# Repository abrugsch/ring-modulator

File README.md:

# ring-modulator
 ring modulator pedal created from https://www.instructables.com/Ring-Modulator-Pedal/

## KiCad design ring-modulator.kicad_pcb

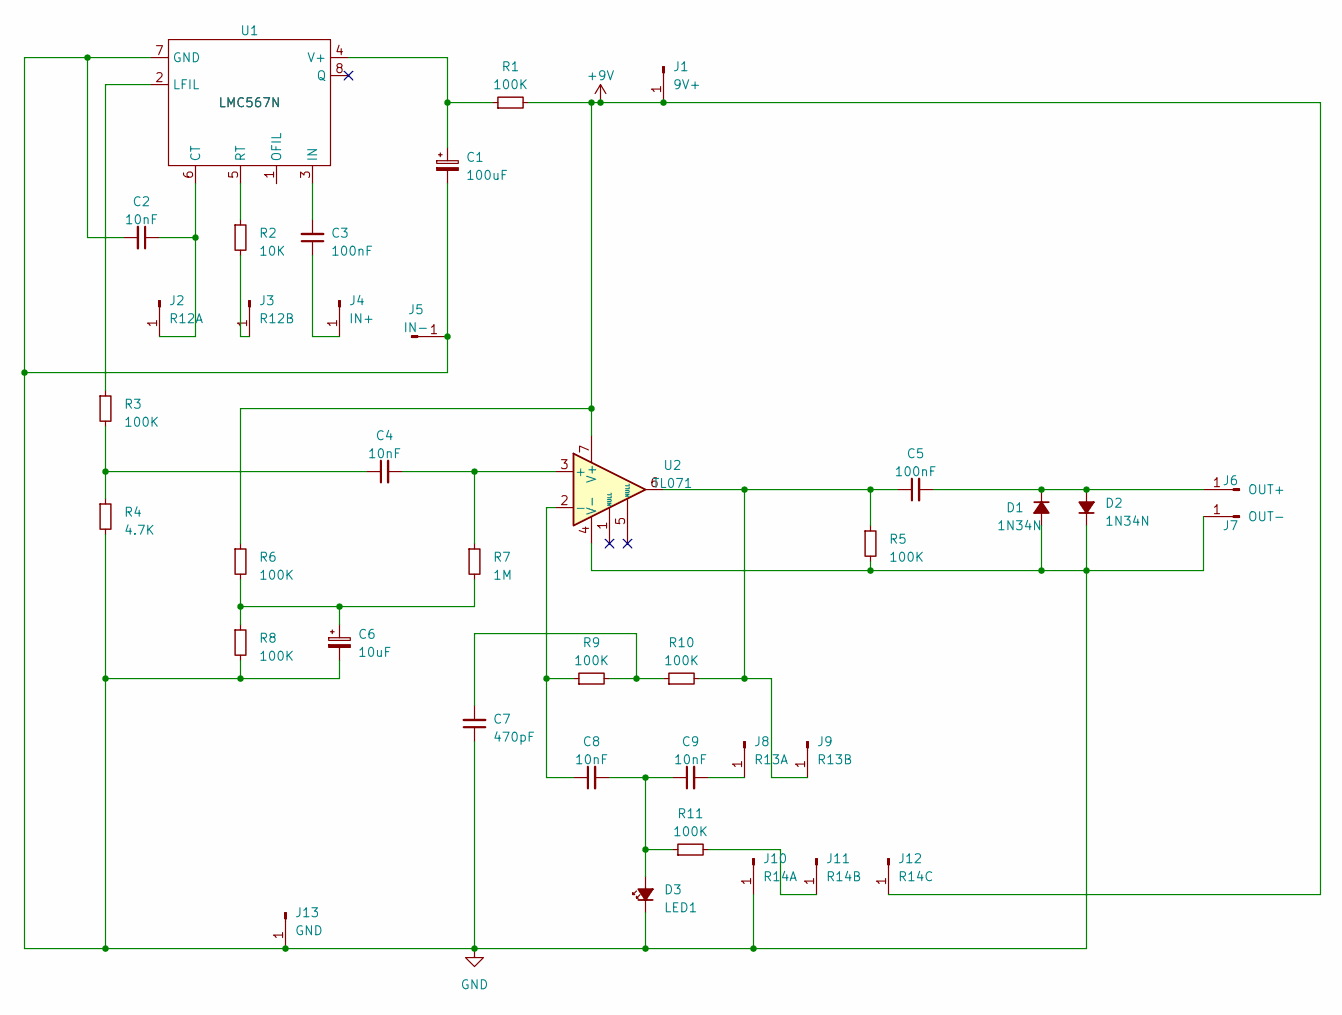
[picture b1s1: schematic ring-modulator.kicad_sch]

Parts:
C1: 100uF; CP_Radial_D8.0mm_P3.50mm
C2, C4, C8, C9: 10nF; C_Disc_D3.0mm_W2.0mm_P2.50mm
C3, C5: 100nF; C_Disc_D4.3mm_W1.9mm_P5.00mm
C6: 10uF; CP_Radial_D5.0mm_P2.50mm
C7: 470pF; C_Disc_D3.0mm_W2.0mm_P2.50mm
D1, D2: 1N34N; D_DO-35_SOD27_P7.62mm_Horizontal
D3: LED1; LED_D5.0mm
J1: 9V+; PinSocket_1x01_P2.54mm_Vertical
J2: R12A; PinSocket_1x01_P2.54mm_Vertical
J3: R12B; PinSocket_1x01_P2.54mm_Vertical
J4: IN+; PinSocket_1x01_P2.54mm_Vertical
J5: IN-; PinSocket_1x01_P2.54mm_Vertical
J6: OUT+; PinSocket_1x01_P2.54mm_Vertical
J7: OUT-; PinSocket_1x01_P2.54mm_Vertical
J8: R13A; PinSocket_1x01_P2.54mm_Vertical
J9: R13B; PinSocket_1x01_P2.54mm_Vertical
J10: R14A; PinSocket_1x01_P2.54mm_Vertical
J11: R14B; PinSocket_1x01_P2.54mm_Vertical
J12: R14C; PinSocket_1x01_P2.54mm_Vertical
J13: GND; PinSocket_1x01_P2.54mm_Vertical
R1, R3, R5, R6, R8, R9, R10, R11: 100K; R_Axial_DIN0207_L6.3mm_D2.5mm_P7.62mm_Horizontal
R2: 10K; R_Axial_DIN0207_L6.3mm_D2.5mm_P7.62mm_Horizontal
R4: 4.7K; R_Axial_DIN0207_L6.3mm_D2.5mm_P7.62mm_Horizontal
R7: 1M; R_Axial_DIN0207_L6.3mm_D2.5mm_P7.62mm_Horizontal
U1: LMC567N; DIP-8_W7.62mm
U2: TL071; DIP-8_W7.62mm

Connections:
+9V: J1.1, J12.1, R1.2, R6.1, U2.7 (V+)
GND: C1.2, C2.2, C6.2, C7.1, D1.2 (A), D2.1 (K), D3.1 (K), J5.1, J7.1, J10.1, J13.1, R4.2, R5.2, R8.2, U1.7 (GND), U2.4 (V-)
unnamed: C4.1, R3.2, R4.1
unnamed: C6.1, R6.2, R7.2, R8.1
unnamed: C7.2, R9.2, R10.1
unnamed: C5.2, D1.1 (K), D2.2 (A), J6.1
unnamed: C8.2, C9.1, D3.2 (A), R11.1
unnamed: C2.1, J2.1, U1.6 (CT)
unnamed: J3.1, R2.2
unnamed: C3.1, J4.1
unnamed: C9.2, J8.1
unnamed: C5.1, J9.1, R5.1, R10.2, U2.6
unnamed: J11.1, R11.2
unnamed: C3.2, U1.3 (IN)
unnamed: R3.1, U1.2 (LFIL)
unnamed: R2.1, U1.5 (RT)
unnamed: C1.1, R1.1, U1.4 (V+)
unnamed: C4.2, R7.1, U2.3 (+)
unnamed: C8.1, R9.1, U2.2 (-)

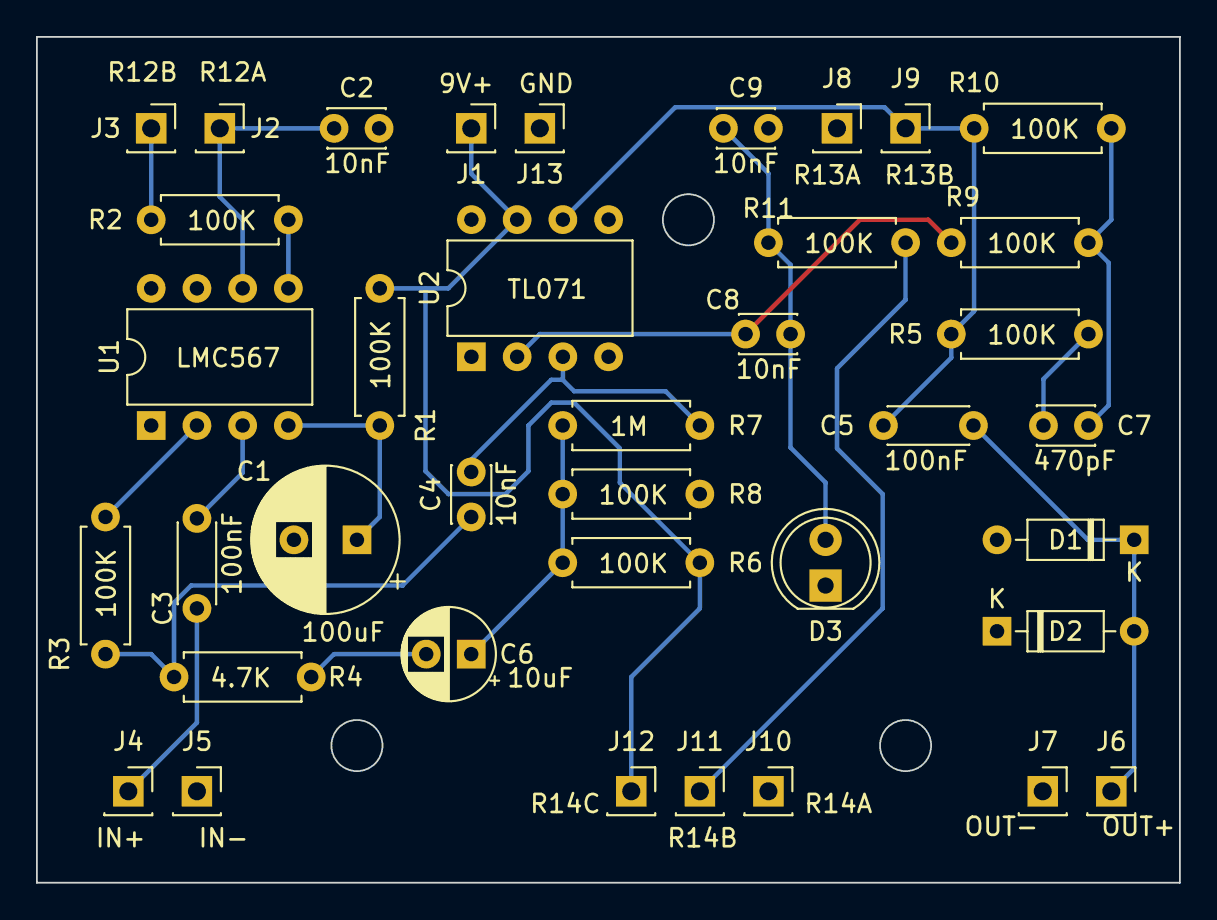
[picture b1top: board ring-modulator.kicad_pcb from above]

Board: 2 copper layers, 63.5 x 47.0 mm, 38 parts (0 on the bottom side), 19 nets.

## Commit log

2023-11-29 initial file checkin
    V0.1 of the Ring modulator PCB
